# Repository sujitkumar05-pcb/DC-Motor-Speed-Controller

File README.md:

# DC-Motor-Speed-Controller

PCB designed to control the speed of a DC motor.

Uses PWM (Pulse Width Modulation) to adjust motor speed.

Includes components like MOSFETs or transistors for switching.

Compatible with microcontrollers for easy control.

Suitable for robotics, automation, and DIY motor projects.

# a to z

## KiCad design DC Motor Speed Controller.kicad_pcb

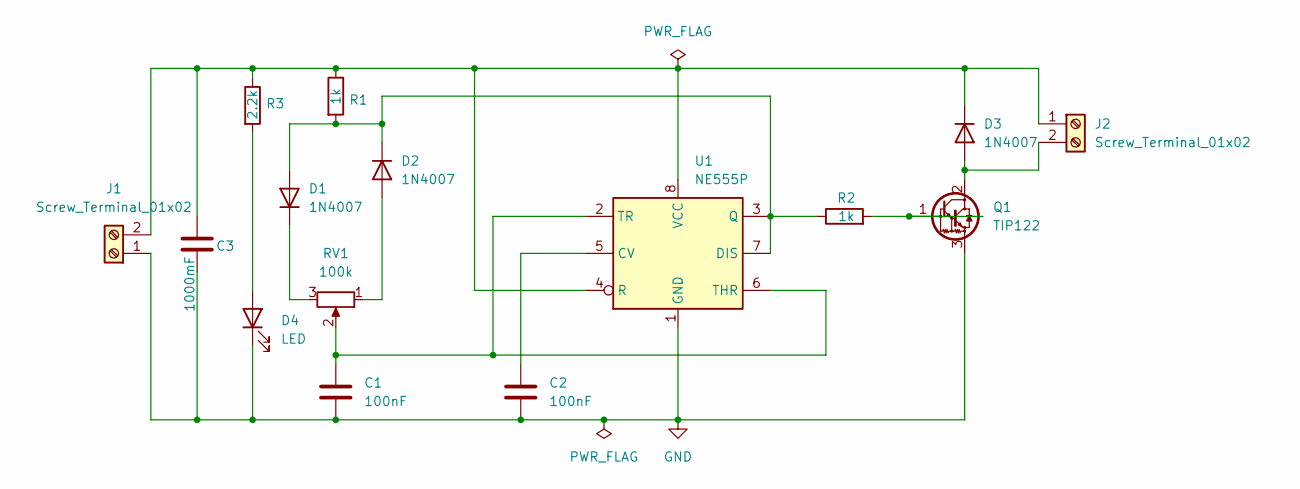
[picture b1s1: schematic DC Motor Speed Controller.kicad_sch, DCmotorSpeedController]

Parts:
C1, C2: 100nF; C_Disc_D4.7mm_W2.5mm_P5.00mm
C3: 1000mF; CP_Radial_D10.0mm_P5.00mm
D1, D2, D3: 1N4007; D_DO-41_SOD81_P10.16mm_Horizontal
D4: LED; LED_D5.0mm
J1, J2: Screw_Terminal_01x02; TerminalBlock_bornier-2_P5.08mm
Q1: TIP122; TO-220-3_Vertical
R1, R2: 1k; R_Axial_DIN0204_L3.6mm_D1.6mm_P7.62mm_Horizontal
R3: 2.2k; R_Axial_DIN0204_L3.6mm_D1.6mm_P7.62mm_Horizontal
RV1: 100k; Potentiometer_Alps_RK163_Single_Horizontal
U1: NE555P; DIP-8_W7.62mm

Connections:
GND: C1.2, C2.2, C3.2, D4.1 (K), J1.1, Q1.3 (E), U1.1 (GND)
unnamed: D1.2 (A), D2.1 (K), R1.2, R2.1, U1.3 (Q), U1.7 (DIS)
unnamed: D1.1 (K), RV1.3
unnamed: D2.2 (A), RV1.1
unnamed: D3.2 (A), J2.2, Q1.2 (C)
unnamed: C3.1, D3.1 (K), J1.2, J2.1, R1.1, R3.1, U1.4 (R), U1.8 (VCC)
unnamed: D4.2 (A), R3.2
unnamed: Q1.1 (B), R2.2
unnamed: C2.1, U1.5 (CV)
unnamed: C1.1, RV1.2, U1.2 (TR), U1.6 (THR)

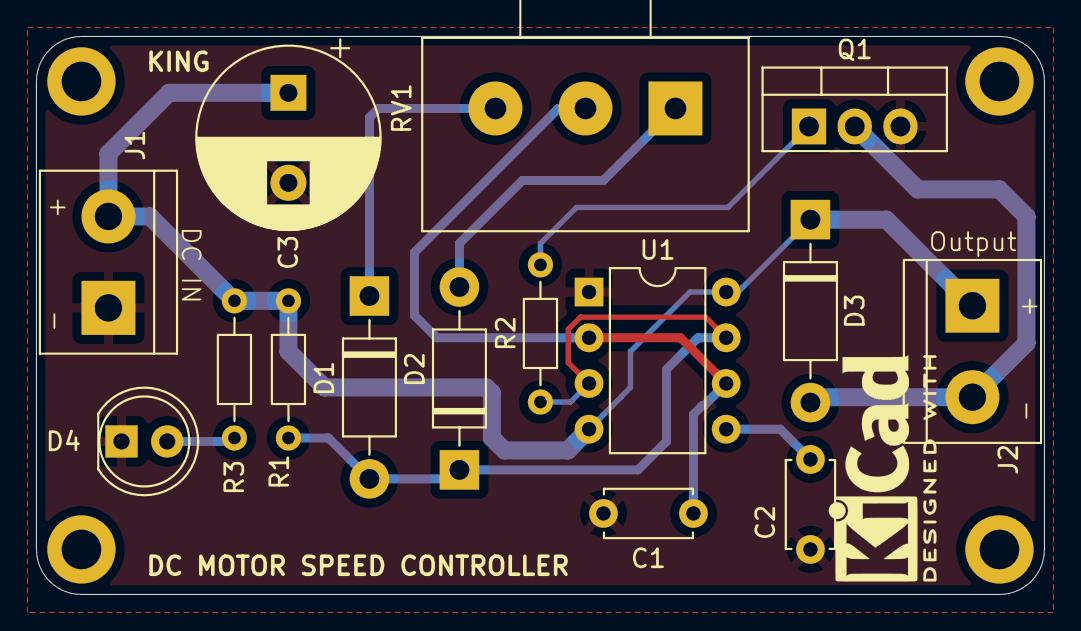
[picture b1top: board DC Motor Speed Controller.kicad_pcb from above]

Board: 2 copper layers, 56.0 x 31.0 mm, 15 parts (0 on the bottom side), 10 nets.
